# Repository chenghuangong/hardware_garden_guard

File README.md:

# hardware_garden_guard
esp8266 was used to pump water, monit temperture and RH

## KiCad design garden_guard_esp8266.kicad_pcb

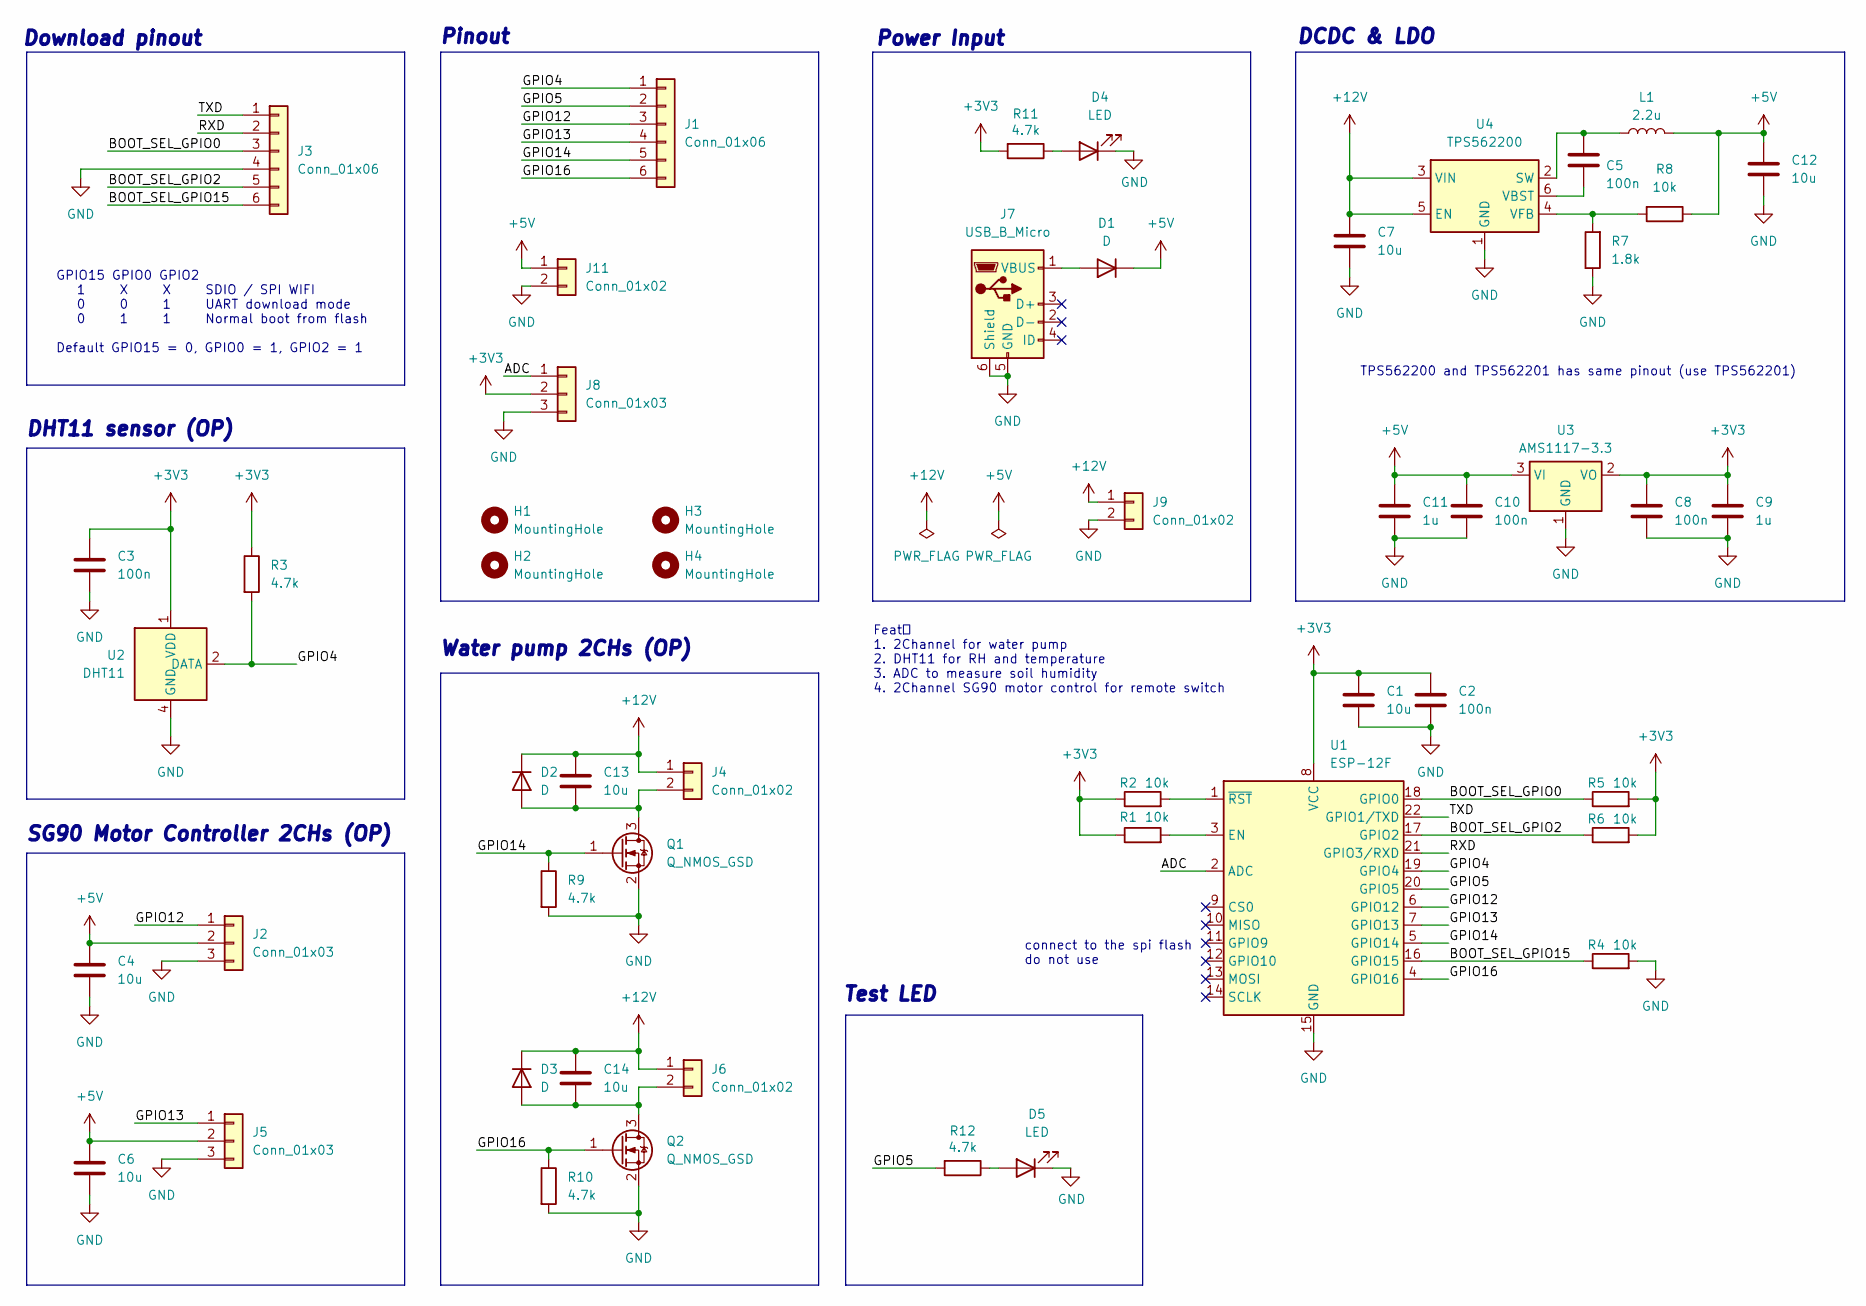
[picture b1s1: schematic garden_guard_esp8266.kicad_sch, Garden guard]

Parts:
C1, C4, C6, C12: 10u; C_0603_1608Metric
C2, C3, C5, C8, C10: 100n; C_0603_1608Metric
C7, C13, C14: 10u; C_0805_2012Metric
C9, C11: 1u; C_0603_1608Metric
D1, D2, D3: D; D_SOD-323
D4, D5: LED; LED_0603_1608Metric
H1, H2, H3, H4: MountingHole; MountingHole_2.7mm_M2.5_Pad_Via
J1, J3: Conn_01x06; PinHeader_1x06_P2.54mm_Vertical
J2, J5, J8: Conn_01x03; PinHeader_1x03_P2.54mm_Vertical
J4, J6: Conn_01x02; PinHeader_1x02_P2.54mm_Vertical
J7: USB_B_Micro; USB_Micro-B_Molex-105017-0001
J9, J11: Conn_01x02; XH2.54_1x02_P2.54mm_H
L1: 2.2u; L_Sunlord_SWPA3012S
Q1, Q2: Q_NMOS_GSD; SOT-23
R1, R2, R4, R5, R6, R8: 10k; R_0603_1608Metric
R3, R9, R10, R11, R12: 4.7k; R_0603_1608Metric
R7: 1.8k; R_0603_1608Metric
U1: ESP-12F; ESP-12E
U2: DHT11; Aosong_DHT11_5.5x12.0_P2.54mm
U3: AMS1117-3.3; SOT-223-3_TabPin2
U4: TPS562200; SOT-23-6

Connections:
+3V3: C1.1, C2.1, C3.1, C8.1, C9.1, J8.2, R1.1, R2.1, R3.1, R5.2, R6.2, R11.2, U1.8 (VCC), U2.1 (VDD), U3.2 (VO)
+5V: C4.1, C6.1, C10.1, C11.1, C12.1, D1.1 (K), J2.2, J5.2, J11.1, L1.2, R8.1, U3.3 (VI)
+12V: C7.1, C13.1, C14.1, D2.1 (K), D3.1 (K), J4.1, J6.1, J9.1, U4.3 (VIN), U4.5 (EN)
/ADC: J8.1, U1.2 (ADC)
/BOOT_SEL_GPIO0: J3.3, R5.1, U1.18 (GPIO0)
/BOOT_SEL_GPIO2: J3.5, R6.1, U1.17 (GPIO2)
/BOOT_SEL_GPIO15: J3.6, R4.1, U1.16 (GPIO15)
/GPIO4: J1.1, R3.2, U1.19 (GPIO4), U2.2 (DATA)
/GPIO5: J1.2, R12.2, U1.20 (GPIO5)
/GPIO12: J1.3, J2.1, U1.6 (GPIO12)
/GPIO13: J1.4, J5.1, U1.7 (GPIO13)
/GPIO14: J1.5, Q1.1 (G), R9.1, U1.5 (GPIO14)
/GPIO16: J1.6, Q2.1 (G), R10.1, U1.4 (GPIO16)
/RXD: J3.2, U1.21 (GPIO3/RXD)
/TXD: J3.1, U1.22 (GPIO1/TXD)
GND: C1.2, C2.2, C3.2, C4.2, C6.2, C7.2, C8.2, C9.2, C10.2, C11.2, C12.2, D4.1 (K), D5.1 (K), J2.3, J3.4, J5.3, J7.5 (GND), J7.6 (Shield), J8.3, J9.2, J11.2, Q1.2 (S), Q2.2 (S), R4.2, R7.1, R9.2, R10.2, U1.15 (GND), U2.4 (GND), U3.1 (GND), U4.1 (GND)
unnamed: D1.2 (A), J7.1 (VBUS)
unnamed: C13.2, D2.2 (A), J4.2, Q1.3 (D)
unnamed: C14.2, D3.2 (A), J6.2, Q2.3 (D)
unnamed: D4.2 (A), R11.1
unnamed: D5.2 (A), R12.1
unnamed: R1.2, U1.3 (EN)
unnamed: R2.2, U1.1 (~RST)
unnamed: C5.1, L1.1, U4.2 (SW)
unnamed: C5.2, U4.6 (VBST)
unnamed: R7.2, R8.2, U4.4 (VFB)

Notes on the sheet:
Test LED
SG90 Motor Controller 2CHs (OP)
Power Input
Download pinout
connect to the spi flash do not use
Water pump 2CHs (OP)
DHT11 sensor (OP)
GPIO15 GPIO0 GPIO2 1 X X SDIO / SPI WIFI 0 0 1 UART download mode 0 1 1 Normal boot from flash Default GPIO15 = 0, GPIO0 = 1, GPIO2 = 1
DCDC & LDO
TPS562200 and TPS562201 has same pinout (use TPS562201)
Feat： 1. 2Channel for water pump 2. DHT11 for RH and temperature 3. ADC to measure soil humidity 4. 2Channel SG90 motor control for remote switch
Pinout

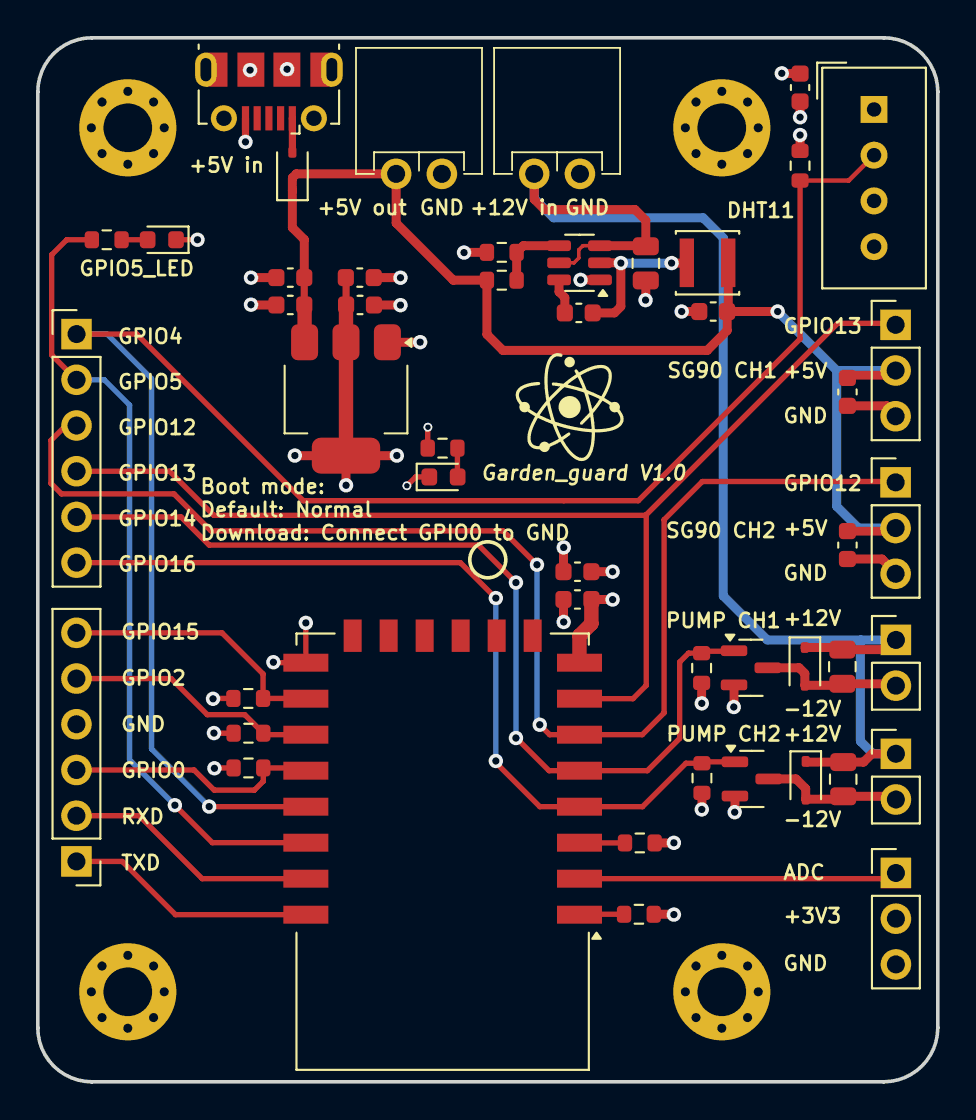
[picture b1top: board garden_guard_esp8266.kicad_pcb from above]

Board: 4 copper layers, 50.0 x 58.0 mm, 52 parts (0 on the bottom side), 26 nets.

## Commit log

2024-07-11 init: Add Garden guard v1.0
